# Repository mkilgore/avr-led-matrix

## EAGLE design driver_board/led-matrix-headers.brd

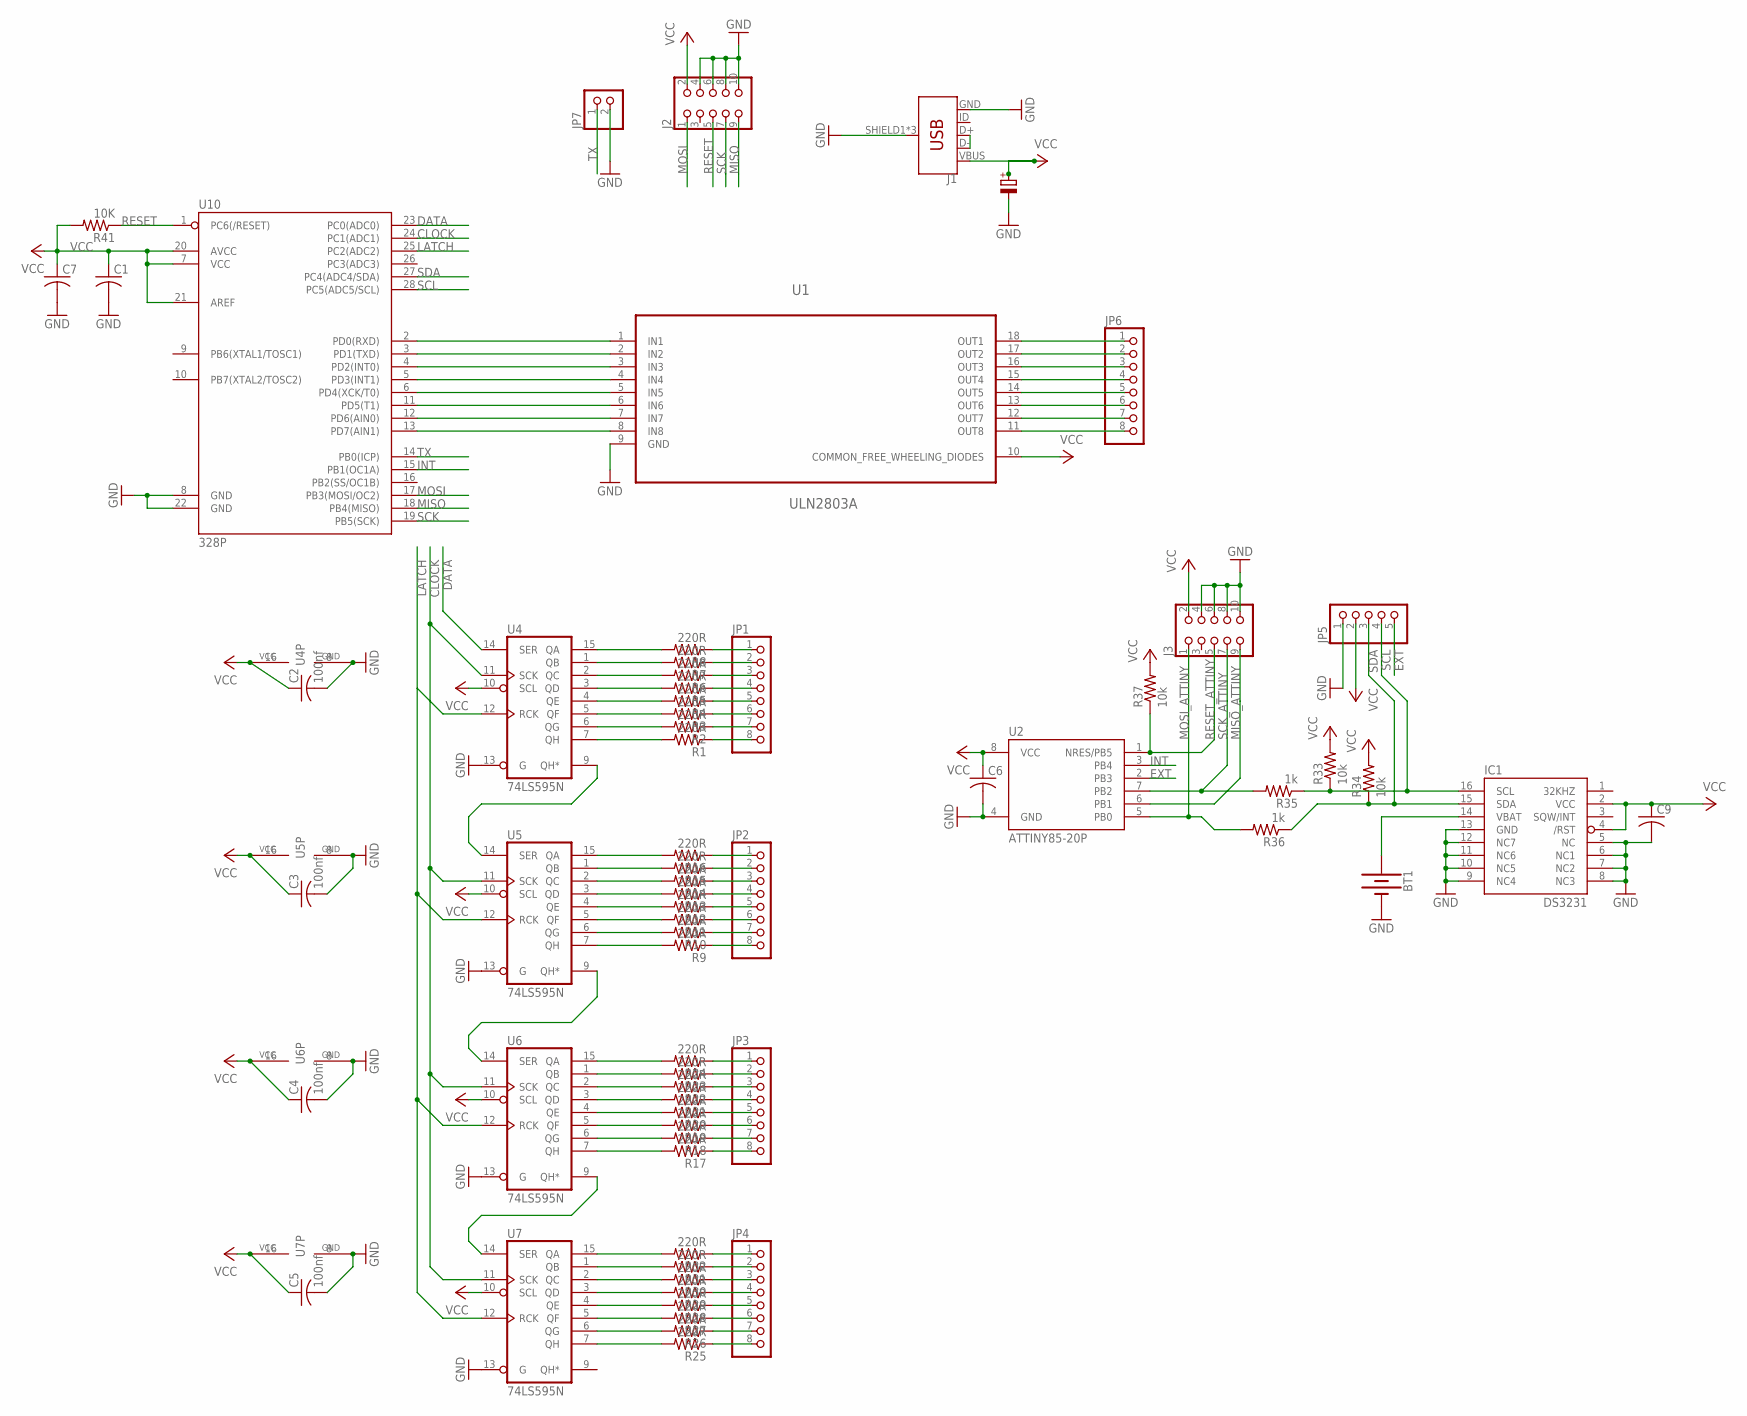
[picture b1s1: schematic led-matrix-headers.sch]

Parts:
BT1: BATTERY-20MM_PTH; BATTCOM_20MM_PTH
C1, C7: C-US025-025X050; C025-025X050
C2, C3, C4, C5: 100nf; C025-025X050
C6, C9: C-US025-024X044; C025-024X044
C8: 10U/35V; E2-5
IC1: DS3231/SO; SO16W
J1: USB_MICRO-B_FEMALE-SMT; USB-B-MICRO-SMD
J2, J3: CON_HEADER_2X05-PTH+SHROUDED_A; PINSHRD_PTH_2X05
JP1, JP2, JP3, JP4, JP6: PINHD-1X8BIG; 1X08-BIG
JP5: PINHD-1X5/OCT; 1X05/OCT
JP7: PINHD-1X02_2.54-S; 1X02-S
R1, R2, R3, R4, R5, R6, R7, R8, R9, R10, R11, R12, R13, R14, R15, R16, R17, R18, R19, R20, R21, R22, R23, R24, R25, R26, R27, R28, R29, R30, R31, R32: 220R; 0204/7
R33, R34, R37: 10k; 0204/7
R35, R36: 1k; 0204/7
R41: 10K; 0204/7
U1: ULN2803A; DIP254P762X393-18
U2: ATTINY85-20P; PDIP08_300MIL
U4, U5, U6, U7: 74LS595N; DIL16
U10: 328P; DIP28

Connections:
CLOCK: U4.11 (SCK), U5.11 (SCK), U6.11 (SCK), U7.11 (SCK), U10.24 (PC1(ADC1))
DATA: U4.14 (SER), U10.23 (PC0(ADC0))
EXT: JP5.5, U2.2 (PB3)
GND: BT1.2 (-), C1.2, C2.2, C3.2, C4.2, C5.2, C6.2, C7.2, C8.-, C9.2, IC1.5 (NC), IC1.6 (NC1), IC1.7 (NC2), IC1.8 (NC3), IC1.9 (NC4), IC1.10 (NC5), IC1.11 (NC6), IC1.12 (NC7), IC1.13 (GND), J1.GND, J1.SHIELD1 (SHIELD), J1.SHIELD2 (SHIELD), J1.SHIELD3 (SHIELD), J2.4, J2.6, J2.8, J2.10, J3.4, J3.6, J3.8, J3.10, JP5.1, JP7.2, U1.9 (GND), U2.4 (GND), U4.8 (GND), U4.13 (G), U5.8 (GND), U5.13 (G), U6.8 (GND), U6.13 (G), U7.8 (GND), U7.13 (G), U10.8 (GND), U10.22 (GND)
INT: U2.3 (PB4), U10.15 (PB1(OC1A))
LATCH: U4.12 (RCK), U5.12 (RCK), U6.12 (RCK), U7.12 (RCK), U10.25 (PC2(ADC2))
MISO: J2.9, U10.18 (PB4(MISO))
MISO_ATTINY: J3.9, U2.6 (PB1)
MOSI: J2.1, U10.17 (PB3(MOSI/OC2))
MOSI_ATTINY: J3.1, R36.2, U2.5 (PB0)
unnamed: JP1.8, R1.1
unnamed: JP1.7, R2.1
unnamed: JP1.6, R3.1
unnamed: JP1.5, R4.1
unnamed: JP1.4, R5.1
unnamed: JP1.3, R6.1
unnamed: JP1.2, R7.1
unnamed: JP1.1, R8.1
unnamed: JP2.8, R9.1
unnamed: JP2.7, R10.1
unnamed: JP2.6, R11.1
unnamed: JP2.5, R12.1
unnamed: JP2.4, R13.1
unnamed: JP2.3, R14.1
unnamed: JP2.2, R15.1
unnamed: JP2.1, R16.1
unnamed: JP3.8, R17.1
unnamed: JP3.7, R18.1
unnamed: JP3.6, R19.1
unnamed: JP3.5, R20.1
unnamed: JP3.4, R21.1
unnamed: JP3.3, R22.1
unnamed: JP3.2, R23.1
unnamed: JP3.1, R24.1
unnamed: JP4.8, R25.1
unnamed: JP4.7, R26.1
unnamed: JP4.6, R27.1
unnamed: JP4.5, R28.1
unnamed: JP4.4, R29.1
unnamed: JP4.3, R30.1
unnamed: JP4.2, R31.1
unnamed: JP4.1, R32.1
unnamed: BT1.1 (+), IC1.14 (VBAT)
unnamed: JP6.1, U1.18 (OUT1)
unnamed: JP6.2, U1.17 (OUT2)
unnamed: JP6.3, U1.16 (OUT3)
unnamed: JP6.4, U1.15 (OUT4)
unnamed: JP6.5, U1.14 (OUT5)
unnamed: JP6.6, U1.13 (OUT6)
unnamed: JP6.7, U1.12 (OUT7)
unnamed: JP6.8, U1.11 (OUT8)
unnamed: R1.2, U4.7 (QH)
unnamed: R2.2, U4.6 (QG)
unnamed: R3.2, U4.5 (QF)
unnamed: R4.2, U4.4 (QE)
unnamed: R5.2, U4.3 (QD)
unnamed: R6.2, U4.2 (QC)
unnamed: R7.2, U4.1 (QB)
unnamed: R8.2, U4.15 (QA)
unnamed: R25.2, U7.7 (QH)
unnamed: R26.2, U7.6 (QG)
unnamed: R27.2, U7.5 (QF)
unnamed: R28.2, U7.4 (QE)
unnamed: R29.2, U7.3 (QD)
unnamed: R30.2, U7.2 (QC)
unnamed: R31.2, U7.1 (QB)
unnamed: R32.2, U7.15 (QA)
unnamed: R17.2, U6.7 (QH)
unnamed: R18.2, U6.6 (QG)
unnamed: R19.2, U6.5 (QF)
unnamed: R20.2, U6.4 (QE)
unnamed: R21.2, U6.3 (QD)
unnamed: R22.2, U6.2 (QC)
unnamed: R23.2, U6.1 (QB)
unnamed: R24.2, U6.15 (QA)
unnamed: R9.2, U5.7 (QH)
unnamed: R10.2, U5.6 (QG)
unnamed: R11.2, U5.5 (QF)
unnamed: R12.2, U5.4 (QE)
unnamed: R13.2, U5.3 (QD)
unnamed: R14.2, U5.2 (QC)
unnamed: R15.2, U5.1 (QB)
unnamed: R16.2, U5.15 (QA)
unnamed: U4.9 (QH*), U5.14 (SER)
unnamed: U5.9 (QH*), U6.14 (SER)
unnamed: U6.9 (QH*), U7.14 (SER)
unnamed: U1.1 (IN1), U10.2 (PD0(RXD))
unnamed: U1.2 (IN2), U10.3 (PD1(TXD))
unnamed: U1.3 (IN3), U10.4 (PD2(INT0))
unnamed: U1.4 (IN4), U10.5 (PD3(INT1))
unnamed: U1.5 (IN5), U10.6 (PD4(XCK/T0))
unnamed: U1.6 (IN6), U10.11 (PD5(T1))
unnamed: U1.7 (IN7), U10.12 (PD6(AIN0))
unnamed: U1.8 (IN8), U10.13 (PD7(AIN1))
RESET: J2.5, R41.1, U10.1 (PC6(/RESET))
RESET_ATTINY: J3.5, R37.1, U2.1 (NRES/PB5)
SCK: J2.7, U10.19 (PB5(SCK))
SCK_ATTINY: J3.7, R35.2, U2.7 (PB2)
SCL: IC1.16 (SCL), JP5.4, R33.1, R35.1, U10.28 (PC5(ADC5/SCL))
SDA: IC1.15 (SDA), JP5.3, R34.1, R36.1, U10.27 (PC4(ADC4/SDA))
TX: JP7.1, U10.14 (PB0(ICP))
USB-DATA: J1.D+, J1.D-
VCC: C1.1, C2.1, C3.1, C4.1, C5.1, C6.1, C7.1, C8.+, C9.1, IC1.2 (VCC), IC1.4 (/RST), J1.VBUS, J2.2, J3.2, JP5.2, R33.2, R34.2, R37.2, R41.2, U1.10 (COMMON_FREE_WHEELING_DIODES), U2.8 (VCC), U4.10 (SCL), U4.16 (VCC), U5.10 (SCL), U5.16 (VCC), U6.10 (SCL), U6.16 (VCC), U7.10 (SCL), U7.16 (VCC), U10.7 (VCC), U10.20 (AVCC), U10.21 (AREF)

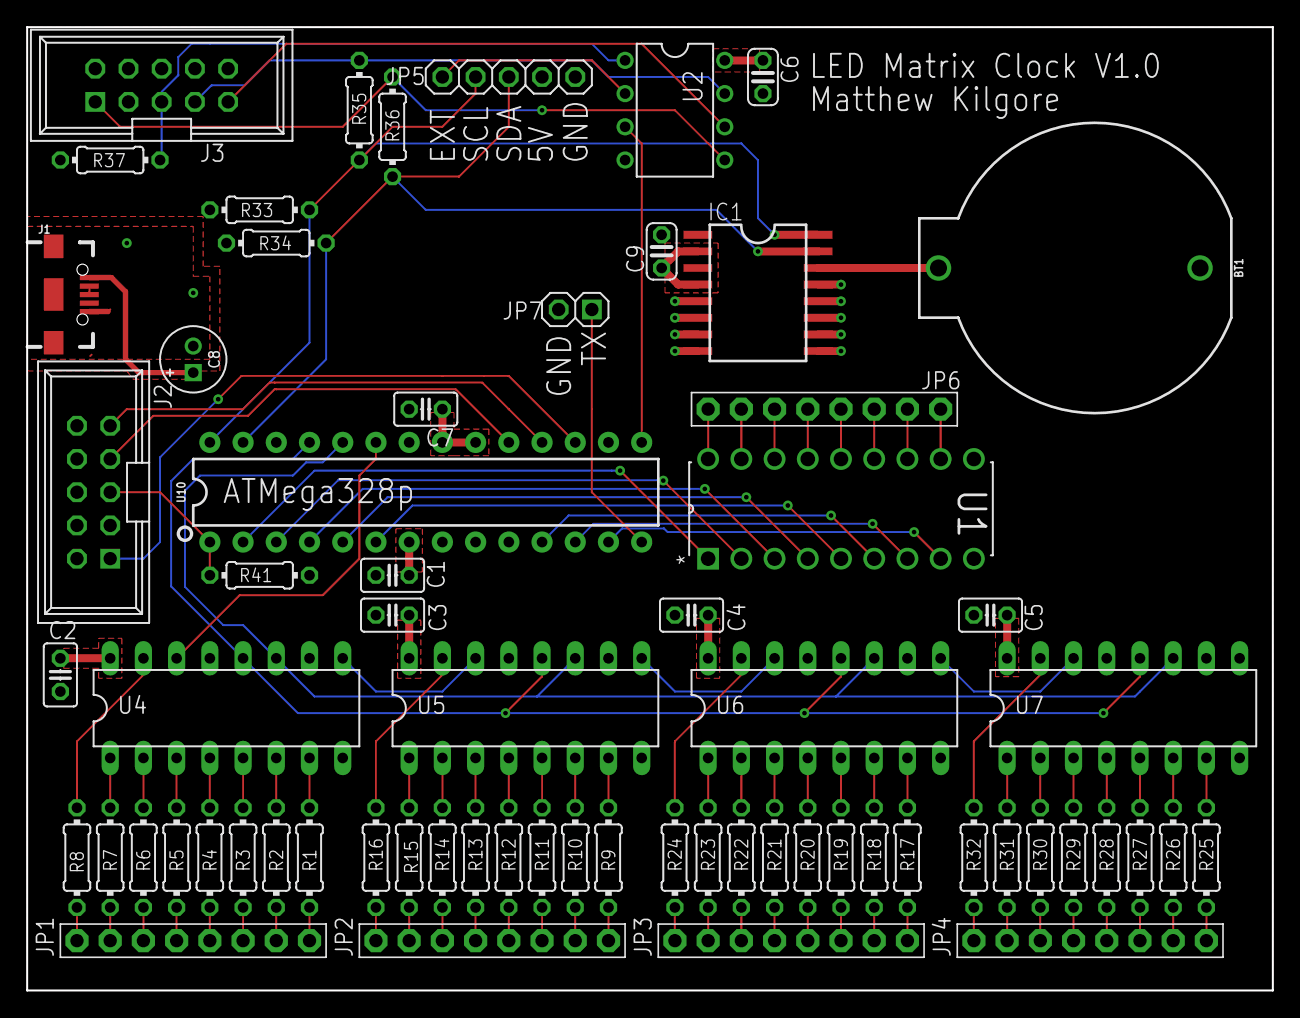
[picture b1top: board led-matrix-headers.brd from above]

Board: 2 copper layers, 95.2 x 73.7 mm, 66 parts (0 on the bottom side), 103 nets.

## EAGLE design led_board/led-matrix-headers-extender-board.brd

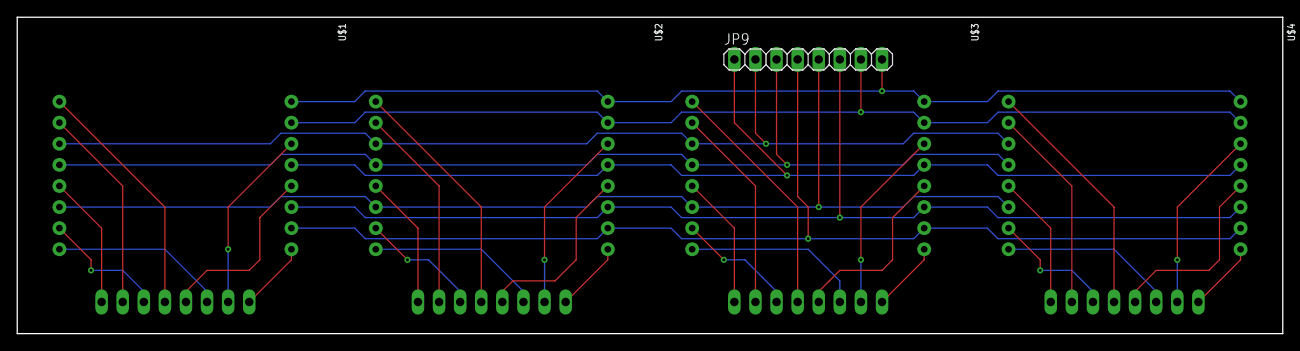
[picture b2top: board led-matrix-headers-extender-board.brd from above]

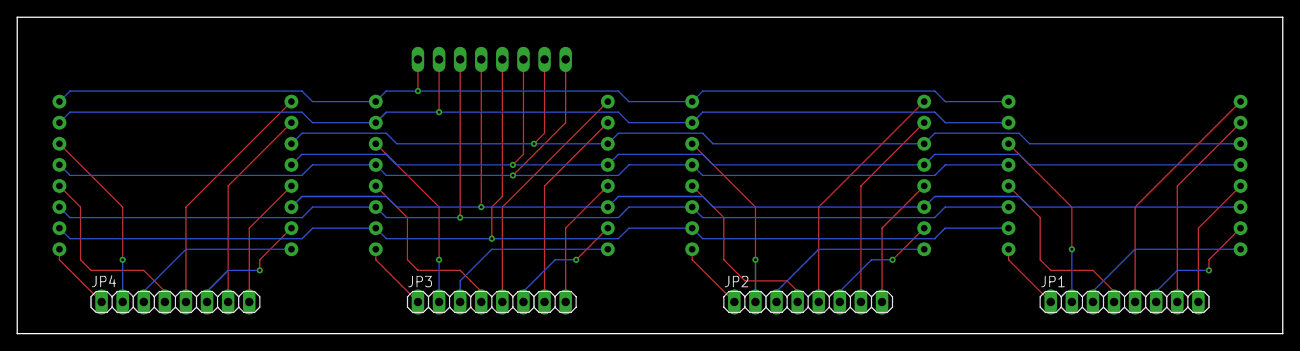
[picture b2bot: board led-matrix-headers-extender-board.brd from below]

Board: 2 copper layers, 152.4 x 38.1 mm, 9 parts (4 on the bottom side), 40 nets.

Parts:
JP1, JP2, JP3, JP4, JP9: 1X08
U$1, U$2, U$3, U$4: ANODEROW_TC15_11SRWA; SEGMENT_TC15-11SRWA

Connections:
unnamed: JP1.1, U$1.9
unnamed: JP1.2, U$1.14
unnamed: JP1.3, U$1.8
unnamed: JP1.4, U$1.12
unnamed: JP1.5, U$1.1
unnamed: JP1.6, U$1.7
unnamed: JP1.7, U$1.2
unnamed: JP1.8, U$1.5
unnamed: JP2.1, U$2.9
unnamed: JP2.2, U$2.14
unnamed: JP2.3, U$2.8
unnamed: JP2.4, U$2.12
unnamed: JP2.5, U$2.1
unnamed: JP2.6, U$2.7
unnamed: JP2.7, U$2.2
unnamed: JP2.8, U$2.5
unnamed: JP3.1, U$3.9
unnamed: JP3.2, U$3.14
unnamed: JP3.3, U$3.8
unnamed: JP3.4, U$3.12
unnamed: JP3.5, U$3.1
unnamed: JP3.6, U$3.7
unnamed: JP3.7, U$3.2
unnamed: JP3.8, U$3.5
unnamed: JP4.1, U$4.9
unnamed: JP4.2, U$4.14
unnamed: JP4.3, U$4.8
unnamed: JP4.4, U$4.12
unnamed: JP4.5, U$4.1
unnamed: JP4.6, U$4.7
unnamed: JP4.7, U$4.2
unnamed: JP4.8, U$4.5
unnamed: JP9.1, U$1.13, U$2.13, U$3.13, U$4.13
unnamed: JP9.2, U$1.3, U$2.3, U$3.3, U$4.3
unnamed: JP9.3, U$1.4, U$2.4, U$3.4, U$4.4
unnamed: JP9.4, U$1.10, U$2.10, U$3.10, U$4.10
unnamed: JP9.5, U$1.6, U$2.6, U$3.6, U$4.6
unnamed: JP9.6, U$1.11, U$2.11, U$3.11, U$4.11
unnamed: JP9.7, U$1.15, U$2.15, U$3.15, U$4.15
unnamed: JP9.8, U$1.16, U$2.16, U$3.16, U$4.16

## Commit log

2018-09-19 Initial code and schematic
2018-10-06 Added DS3231 code and digit scrolling
2018-10-06 Update ATMega code for actual PCB
2018-10-06 Small updates to LED Matrix driver board
2018-10-06 Add eagle board for LED Matrix modules
2018-10-06 atmega328_driver: Dim matrix a little bit
    The matrix is a bit too bright. If doing a rebuild the resistors should
    simply be changed for a higher value, however this change dims them via
    software by leaving them off for a short time rather then keeping them
    on almost constantly.

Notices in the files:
parts and their libraries:
SparkFun-IC-Microcontroller: Licensing: Creative Commons ShareAlike 4.0 International - https://creativecommons.org/licenses/by-sa/4.0
